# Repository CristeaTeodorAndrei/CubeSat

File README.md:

# CubeSat

## Introduction

### About CubeSat

A CubeSat is a compact but sophisticated space platform, meticulously engineered to achieve its scientific goals. These miniaturised satellites are created with precision and purpose, representing a cost-effective and efficient approach to space exploration. Their primary role involves specific scientific, technological or educational missions. <br>
Equipped with payloads, sensors and specialised instruments, CubeSats are deployed to collect critical data, monitor phenomena or conduct experiments in space. Their modular nature allows for versatility, enabling CubeSats to address a wide range of research objectives, from observing Earth to studying cosmic phenomena. <br>
They contribute to advancing our understanding of the cosmos, demonstrating that innovation can thrive even within the confines of a compact form factor.

### About the project

The project was developed with the objective of understanding the complexity of space systems, approaching the different problems that arise in this field and solving them in the most energy and cost efficient way. <br>
The future of this project consists in creating a stable platform that allows future improvements so that young students in this domain can develop.

## CubeSat specifications

### Hardware specs

    1. Raspberry PI 4 Model B
    2. MPU6050 Accelerometer and Gyroscope Sensor
    3. BMP280 Pressure Sensor
    4. Raspberry Pi Camera Module 2
    5. NRF20L01 Wireless Module
    6. Battery System UPS 

### Software specs

OBSW was developed in Python, and the operating system on which the software runs is Raspberian on which some software optimizations have been applied.  <br>
The project is structured in 4 phases:

- Activating Remote Control Phase
- Optimization phase
- Testing phase
- OBSW phase

<br>
Each of these phases has a well-defined objective and must be fulfilled before the final code runs.

## Guideline

### Activating Remote Control Phase

Keep in mind that each script that will run will be sent as a command through the GCM. <br>

Power on the GCM, run the script and open the receiver Interface.

- The Interface should prompt a successful connection message.
- A warning message should appear to notify the failure to connect with the OBC. <br>

Power on the OBC.

- Both GREEN and RED LEDs should be ON indicating that OBC is active and ready for requests.
- A succesful connection message should appear on GCM's Interface to ensure that communcations with the OBC is active and can proceed to the optimization phase.

<br>
GCM will try to connect with the OBC every 5 seconds.

### Optimization Phase

In order to reduce energy usage and ensure efficient performance of the whole system, a number of optimizations have been implemented:

- Deactivating Wi-Fi Module
- Deactivating Bluetooth Module
- Deactivating Update Module
- Deactivating UI

By requesting the OBC to run the script <b> Optimization.py</b> via GCM all of those optimizations will be applied and after that the OBC will reboot. <br>
After restarting the system, the GREEN LED will turn ON and RED LED OFF to indicate successful optimization and a confirmation message should appear in GCM's Interface. <br>
<br>
OBC can proceed to the testing phase.

### Testing Phase

By requesting the OBC to run the script <b>Test.py</b>, the OBC begins testing sequence and a custom TM is sent back to the GCM that indicates the sensors has been detected. <br>
If the RFM is not working or is not responding the RED LED will blink continuously.<br>
If the RFM is working the GREEN LED will blink continuously and a TM will be send to the GCM with the following format:

- [0x00, 0x00, 0x00, 0x00]

TM's params should have the following values:

1. (First) 0x00 - MPU6050 has been detected.

- 0x01 - MPU6050 has not been detected.

2. (Second) 0x00 - BMP280 has been detected.

- 0x01 - BMP280 has not been detected.

3. (Third) 0x00 - Camera Module has been detected.

- 0x01 - Camera Module has not been detected.

4. (Fourth) 0x00 - Power supply voltage is nominal.

- 0x05 - The OBC is undervoltage and the power supply should be verified.

<br>
If the TM's values are not nominal OBSW will repeat the test every 5 seconds. <br>
OBC can proceed to the running phase or main code.

### Running phase

In the phase of running the main code all CubeSat components should work according to the parameters.
<br><br>
By requesting the OBC to run the main code <b>OBSW.py</b> nominal TMs should appear in GCM's Interface. <br>
As discussed in the SDCard chapter before the CubeSat leaves the range of the GCM the OBSW will send a warning message that it will soon disconnect and the data will be written locally. 
<br><br>
That's the final state for the CubeSat before the flight. 

### TMTC Format

A nominal TM should have the following format:

- [TimeStamp, Voltage, Temperature, Load, AccX, AccY, AccZ, GyroX, GyroY, GyroZ, Altitude, Pressure]

TM's params should have the following values:

1. <b>TimeStamp</b> [seconds] float (Eg. 1.00) and represent the relative time.
2. <b>Voltage</b> float (Eg. 1.2) and represent the core voltage.
3. <b>Temperature</b>[degrees] float (Eg. 57.01) and represent the OBC's temperature.
4. <b>Load</b> [%] integer (Eg. 5%) and represent the OBC's load.
5. <b>Acceleration{X,Y,Z}</b>[m/s^2] float (Eg. 10.32) and represent the acceleration on each axis.
6. <b>Gyro{X,Y,Z}</b>[deg/s] float (Eg. 11.01) and represent the rotation on each axis.
7. <b>Altitude</b>[meters] integer (Eg. 1100) and represent the altitude of the CubeSat.
8. <b>Pressure</b>[hPa] float (Eg. 1013.89) and represent the pressure applied to the CubeSat. <br>

<br>
One TM is sent every 5 seconds. <br>
Keep in mind that TMTC will only be available for a period of time until the CubeSat moves out of range of the GCM.

### SDCard

Cubesat will have a Raspberry Pi Camera Module 2 connected and the record will be stored on the SD Card. <br>
Because the RFM allows communication over a relatively short distance with the GCM the flight parameters will be stored on the OBC's internal SD Card. <br>
The OBSW will notify the approaching maximum range and detect the loss of GCM connection, and the data will be passed in .txt format. <br>

## Acronyms

- OBSW - OnBoard Software
- UI - User Interface
- OBC - OnBoard Computer
- TMTC - Telemetry/Telecommand
- GCM - Ground Communication Module
- RFM - Radio Frequency Module

## About me

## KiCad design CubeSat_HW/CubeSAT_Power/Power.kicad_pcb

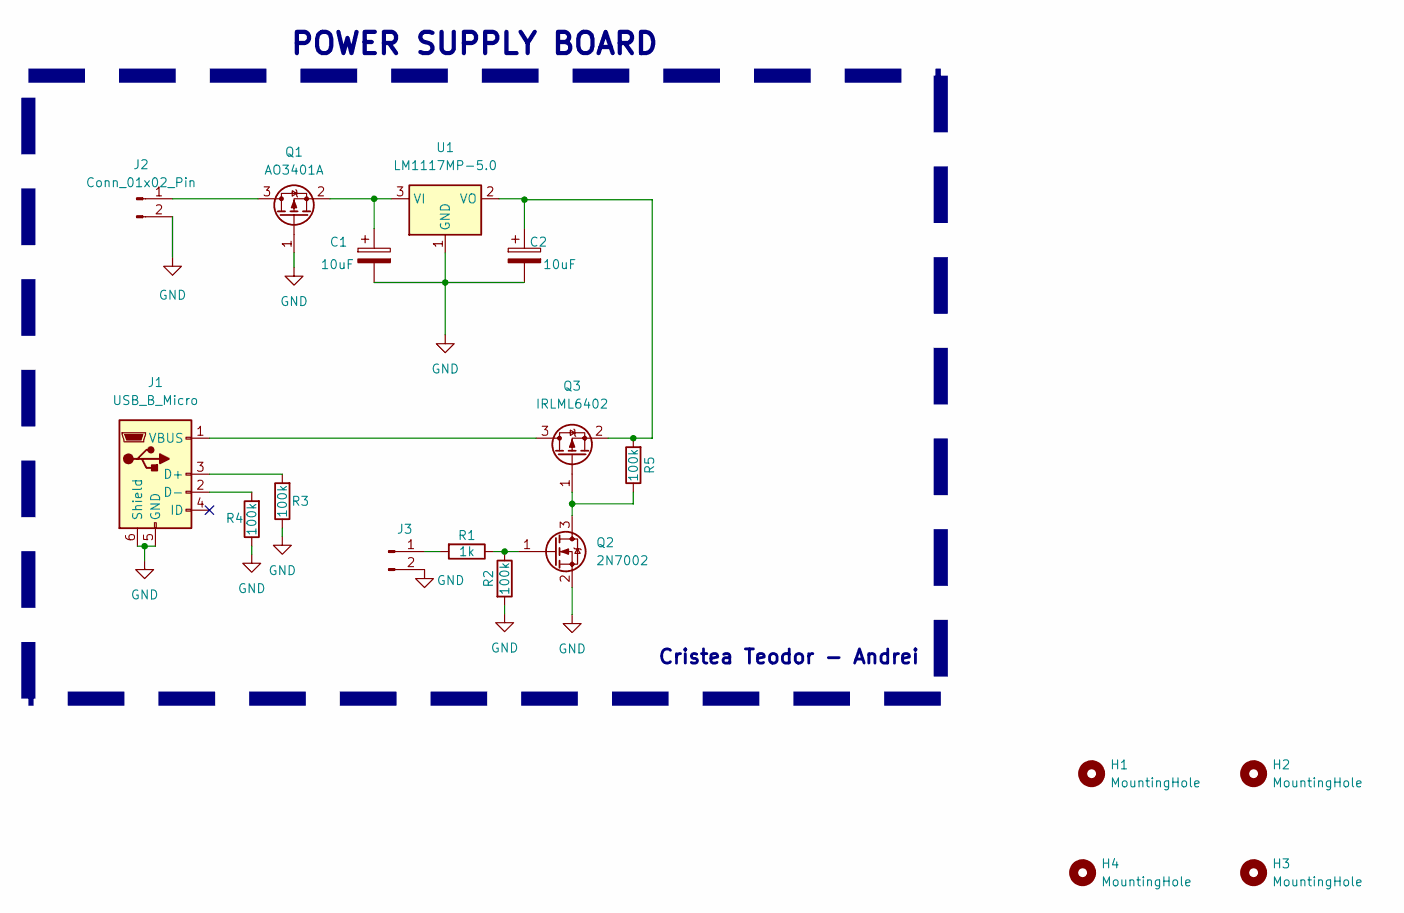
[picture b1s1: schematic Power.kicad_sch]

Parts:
C1, C2: 10uF; CP_EIA-3216-18_Kemet-A
H1, H2, H3, H4: MountingHole; MountingHole_2.7mm
J1: USB_B_Micro; USB_Micro-B_GCT_USB3076-30-A
J2, J3: Conn_01x02_Pin; PinHeader_1x02_P2.54mm_Vertical
Q1: AO3401A; SOT-23
Q2: 2N7002; SOT-23
Q3: IRLML6402; SOT-23
R1: 1k; R_0603_1608Metric
R2, R3, R4, R5: 100k; R_0603_1608Metric
U1: LM1117MP-5.0; SOT-223-3_TabPin2

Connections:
/COMMAND: J3.1, R1.2
GND: C1.2, C2.2, J1.5 (GND), J1.6 (Shield), J2.2, J3.2, Q1.1 (G), Q2.2 (S), R2.2, R3.1, R4.1, U1.1 (GND)
unnamed: J1.3 (D+), R3.2
unnamed: J1.2 (D-), R4.2
unnamed: J1.1 (VBUS), Q3.3 (D)
unnamed: J2.1, Q1.3 (D)
unnamed: C1.1, Q1.2 (S), U1.3 (VI)
unnamed: Q2.3 (D), Q3.1 (G), R5.1
unnamed: Q2.1 (G), R1.1, R2.1
unnamed: C2.1, Q3.2 (S), R5.2, U1.2 (VO)

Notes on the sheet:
POWER SUPPLY BOARD
Cristea Teodor - Andrei

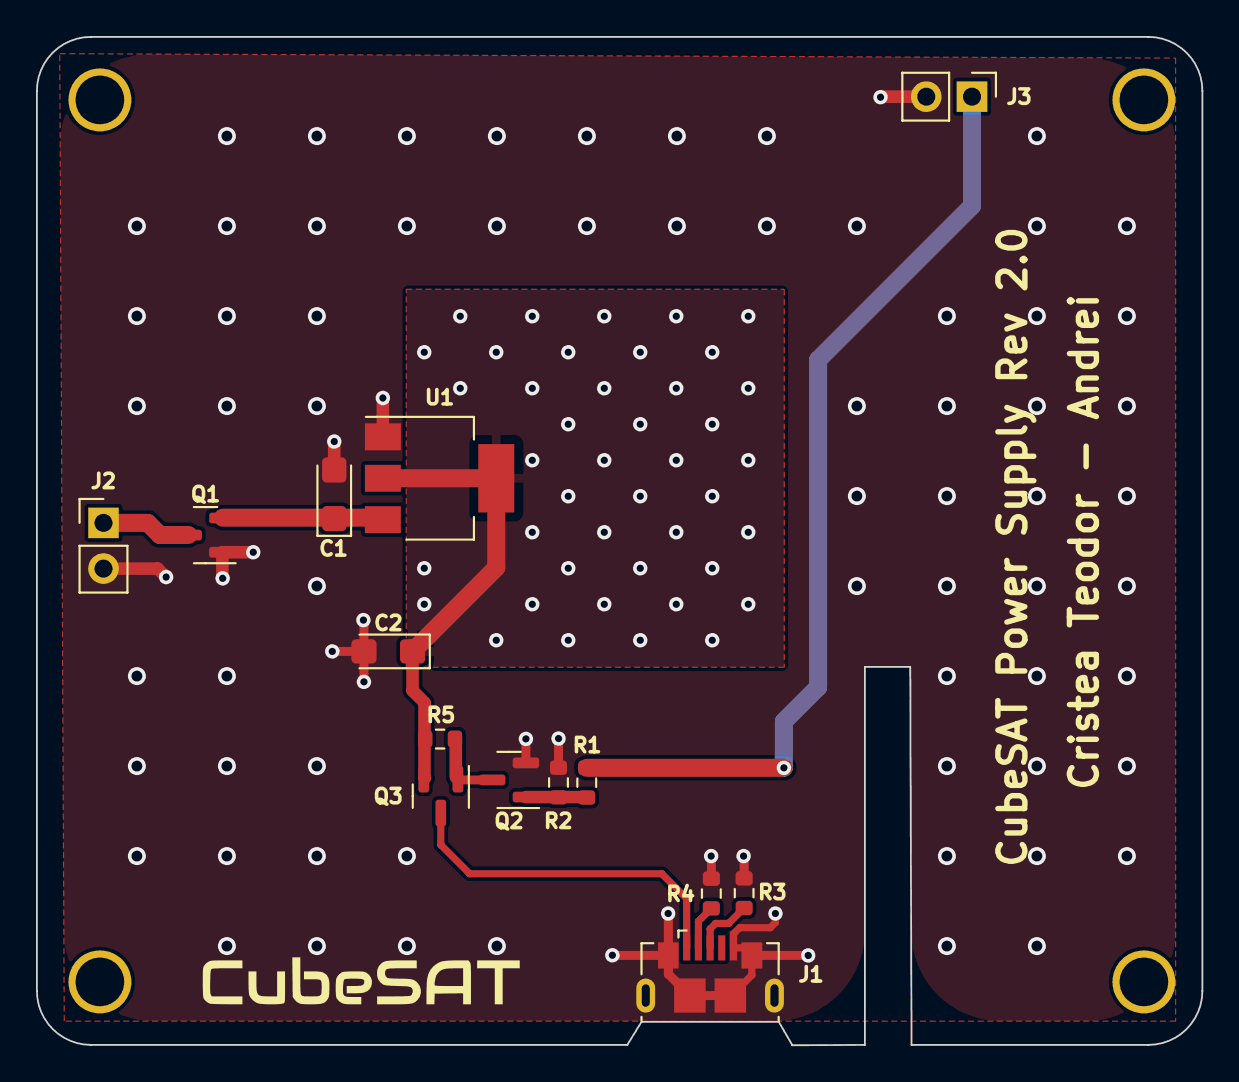
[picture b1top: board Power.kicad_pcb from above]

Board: 2 copper layers, 64.7 x 56.0 mm, 18 parts (0 on the bottom side), 10 nets.

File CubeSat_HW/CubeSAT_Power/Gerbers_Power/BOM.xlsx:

Comment | Designator | Footprint | JLCPCB Part #（optional）
AO3401A | Q1 | SOT-23 | C15127
100k | R4, R3, R2, R5 | R_0603_1608Metric | C25803
LM1117MP-5.0 | U1 | SOT-223-3_TabPin2 | C41202
1k | R1 | R_0603_1608Metric | C21190
10uF | C1, C2 | CP_EIA-3216-18_Kemet-A | C7171
IRLM6402 | Q3 | SOT-23 | C347504
2N7002 | Q2 | SOT-23 | C8545
Micro USB | J1 | Micro USB | C381144

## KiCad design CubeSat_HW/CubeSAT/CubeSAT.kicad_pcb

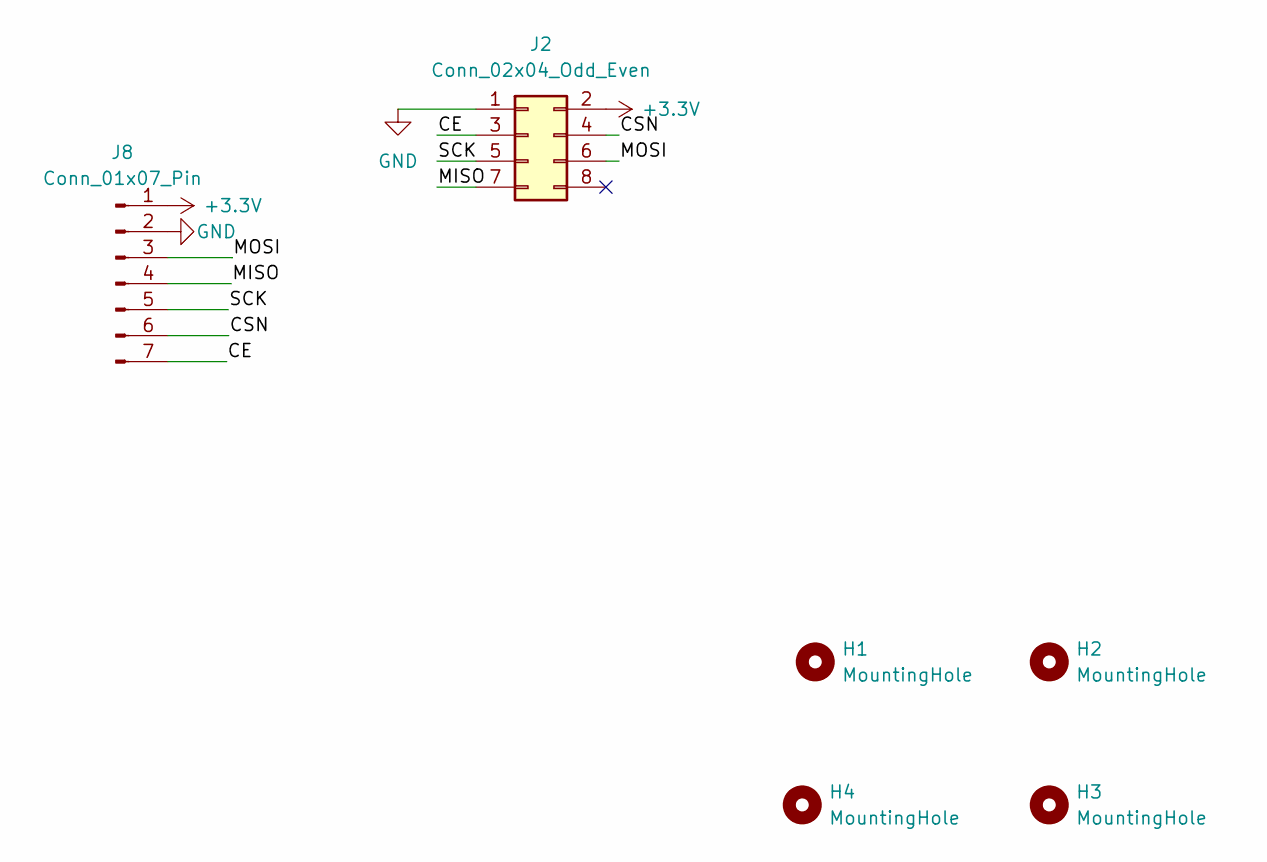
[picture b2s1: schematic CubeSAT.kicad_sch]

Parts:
H1, H2, H3, H4: MountingHole; MountingHole_2.7mm
J2: Conn_02x04_Odd_Even; PinHeader_2x04_P2.54mm_Vertical
J8: Conn_01x07_Pin; PinHeader_1x07_P2.54mm_Horizontal

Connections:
+3.3V: J2.2, J8.1
/CE: J2.3, J8.7
/CSN: J2.4, J8.6
/MISO: J2.7, J8.4
/MOSI: J2.6, J8.3
/SCK: J2.5, J8.5
GND: J2.1, J8.2

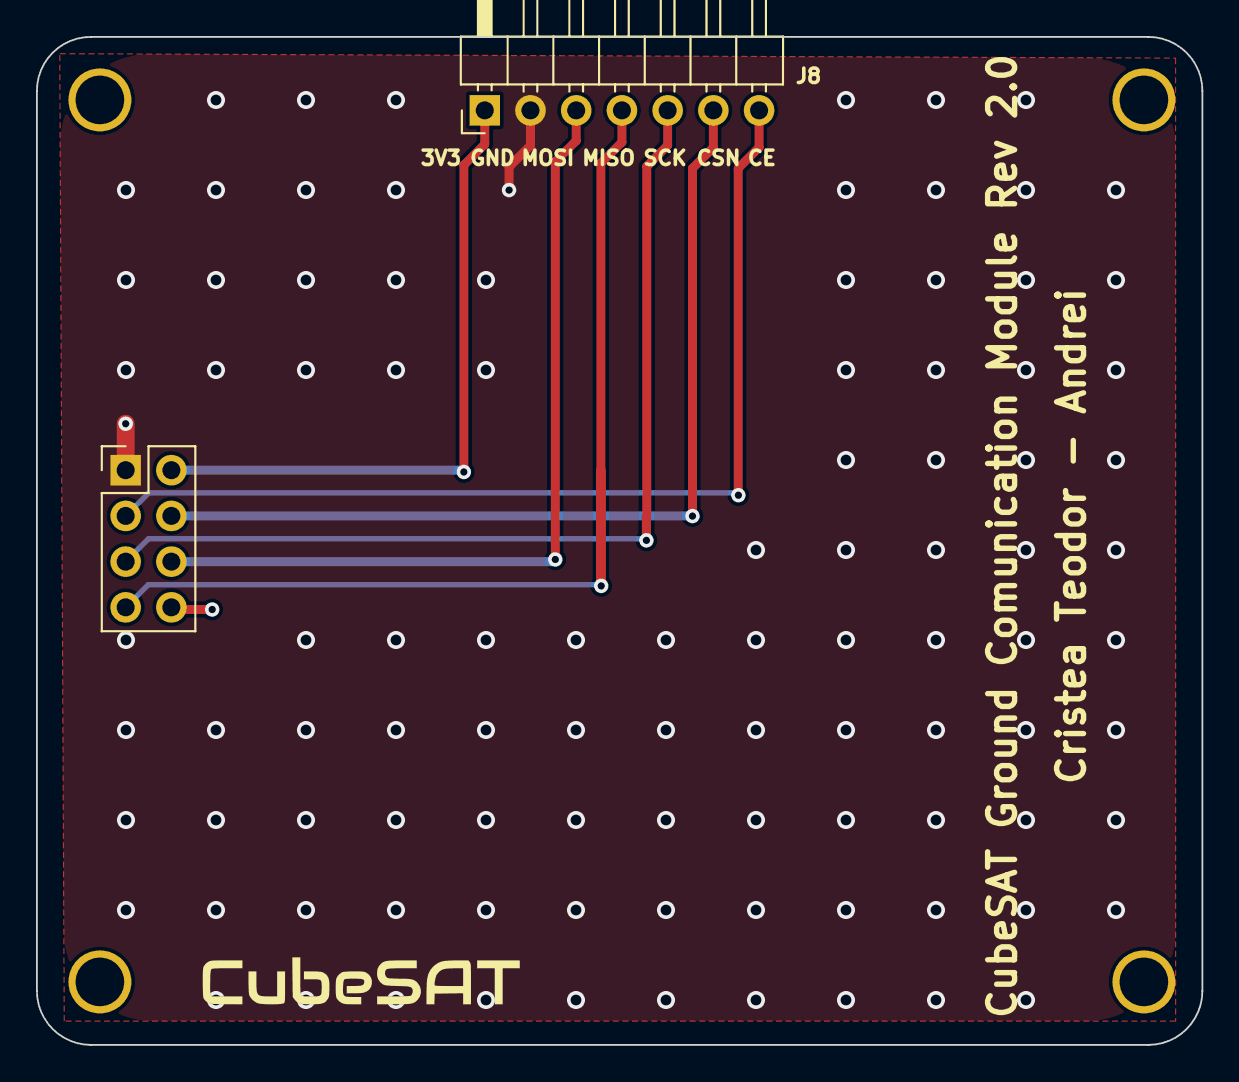
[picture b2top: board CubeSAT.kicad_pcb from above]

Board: 2 copper layers, 64.8 x 56.0 mm, 6 parts (0 on the bottom side), 7 nets.

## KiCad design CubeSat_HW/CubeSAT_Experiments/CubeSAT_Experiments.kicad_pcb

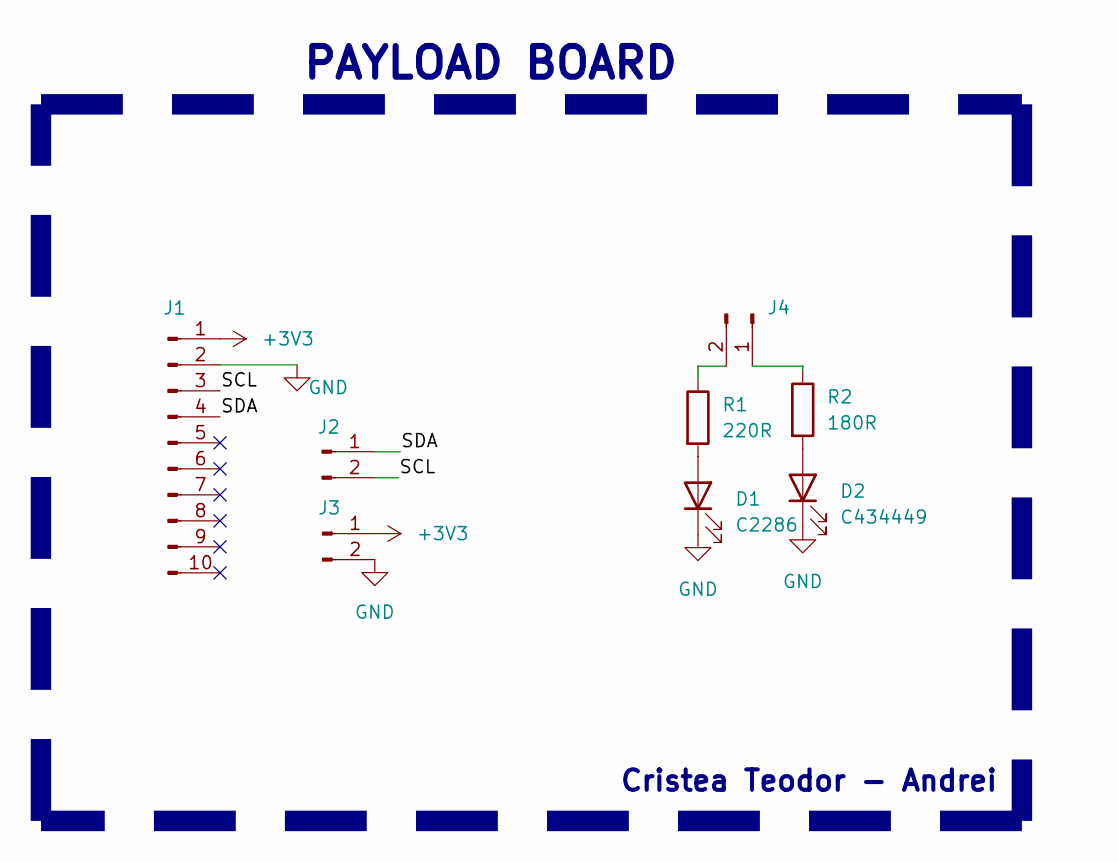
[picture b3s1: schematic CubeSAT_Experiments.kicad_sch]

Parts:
D1: C2286; LED_0603_1608Metric
D2: C434449; LED_0603_1608Metric
J1: Conn_01x10_Pin; PinHeader_1x10_P2.54mm_Vertical
J2, J3, J4: Conn_01x02_Pin; PinHeader_1x02_P2.54mm_Vertical
R1: 220R; R_0603_1608Metric
R2: 180R; R_0603_1608Metric

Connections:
+3V3: J1.1, J3.1
/SCL: J1.3, J2.2
/SDA: J1.4, J2.1
GND: D1.1 (K), D2.1 (K), J1.2, J3.2
unnamed: D1.2 (A), R1.2
unnamed: D2.2 (A), R2.2
unnamed: J4.1, R2.1
unnamed: J4.2, R1.1

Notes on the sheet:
PAYLOAD BOARD
Cristea Teodor - Andrei

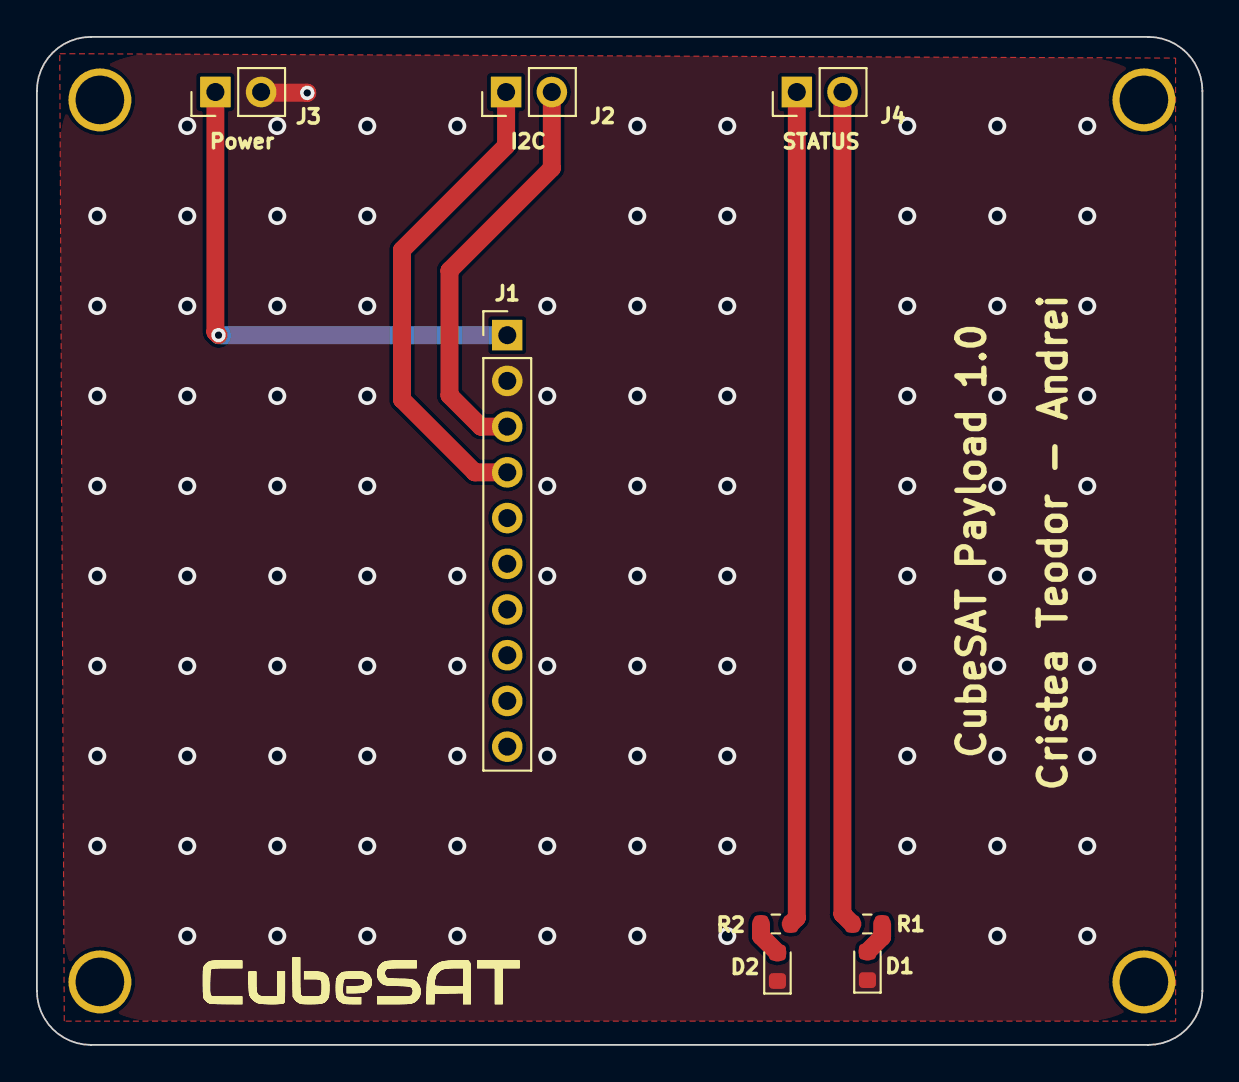
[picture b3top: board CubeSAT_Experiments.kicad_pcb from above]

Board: 2 copper layers, 64.8 x 56.0 mm, 12 parts (0 on the bottom side), 8 nets.

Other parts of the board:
H1, H2, H3, H4: MountingHole; MountingHole_2.7mm

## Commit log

2023-08-20 OS Optimizations
2023-08-20 OS Optimization Wizard
2023-08-20 Main file
2023-08-20 Removed OS.py
2023-08-20 Modified main file
2023-08-25 Updated README file
2023-08-25 Modified README file
2023-08-26 Renamed the main file
2023-08-27 Update README file
2023-10-03 Renamed the optimization script
2023-10-16 Added gitignore file
2023-10-16 Added hardware project
2023-10-30 Added version 2 of the PCB
2023-11-09 feat: Added 3D files for the CubeSAT
2023-11-09 feat: Added Datasheets for the project
2023-11-09 feat: Removed unnecessarily files
2023-11-09 feat: Added Power and Com PCB
2023-11-14 feat: Added new version for the Power Supply Board
2023-11-18 fix: Minor fixes to the Power Supply Board
2023-11-18 release: Added version II of PS project.
2023-11-18 feat: Added GBR, CPL and BOM for PS Board
2023-11-18 feat: Added new version for HW Board
2023-11-30 feat: Minor changes
    Created a special test case to verify if the service has been disabled or not.
2023-11-30 feat: Added GBR, BOM, CPL files for the project
2023-11-30 feat: Added photos with each modules
2023-11-30 fix: Small changes
2023-11-30 feat: Major updates to the optimization phase
2023-11-30 fix: The user cannot see the events for testing
2023-11-30 fix: Wrong function parameter sent
2023-11-30 fix: Misspelled argument
2023-11-30 fix: Set the python installer to quiet mode.
2023-11-30 fix: Set the optimize to return the error code, not the entire line
2023-11-30 feat: Removed hciuart
2023-11-30 feat: Removed bash folder and sh code.
2023-11-30 fix: Small fixes
2023-11-30 fix: Minor visual changes
2023-11-30 feat: Added rebooting condition
2023-11-30 fix: Minor fixes
2023-11-30 fix: Visual improvements
2023-11-30 fix: Trying to fix VM restarting error
2023-11-30 fix: Trying to solve VM restarting error
2023-11-30 fix: Rebased (try #0)
2023-11-30 fix: Rebase (try #1)
2023-11-30 fix: Rebase (#try 2)
2023-11-30 fix: Rebase (#3)
2023-11-30 fix: Rebase (#4)
2023-11-30 fix: Rebase #5
2023-11-30 fix: Rebase (#6)
2023-11-30 fix: Rebase (#7)
2023-11-30 fix: Rebase (#8)
2023-12-01 fix: Fixing Updates function
2023-12-01 fix: Fixed Bluetooth function
2023-12-01 fix: Fixed GUI function
2023-12-01 feat: Trying to fix GUI crashing error.
2023-12-01 fix: Removed the terminal infos
2023-12-01 fix: Trying to fix GUI error (#000)
2023-12-01 fix: Trying to fix GUI error (#001)
2023-12-01 fix: Trying to fix GUI error (#002)
2023-12-01 release: Fixed GUI problem! {Explanation}
2023-12-01 fix: Minor changes
2023-12-01 feat: Trying to add reboot condition.
2023-12-01 fix: Trying to add Reboot condition
2023-12-01 Release: Optimization stage finished (#000)
    COMM PROTOCOLS and DISABLE WI-FI have been commented because I cannot emulate them in VM.
    Future testing phases should be done.
2023-12-22 Updated Optimization.py file
2023-12-23 Release: U&T the Optimization file
2023-12-23 Release: U&T Optimization file (0.010)
2023-12-23 Release: U&T Optimization file (1.000)
2023-12-24 feat: Added Nominal function (0.000)
2024-03-09 feat: Added Nominal.py
2024-03-11 feat: Added Payload Board and new Gerbers for the project
2024-03-11 fix: Fixed indentation in the code for better view
2024-04-22 feat: Added GUI for the app
2024-05-22 Updated Nominal.py -- final version
2024-05-22 Released main.py
2024-05-23 feat: Updated the Get_Data.py to store the array that comes from CubeSAt
2024-05-23 fix: Updated the Ping to run much faster
2024-05-23 feat: Created Raw.py file
2024-05-23 Deleted CubeSat_SW/Raw.py
2024-05-23 fix: Updated GUI.py with new buttons
2024-05-23 feat: Delete ping copied file
2024-05-23 feat: Create Render.py (not stable)
2024-05-24 feat: Updated the Raw.py
    Fixed a bug that prevents the buffer to get empty after a lost connection.
2024-05-25 Release: Fixed a bug inside the code
2024-06-04 fix: Updated main.py
2024-06-06 Release: main.py
2024-06-06 Release: main.py
2024-06-11 Release main.py
